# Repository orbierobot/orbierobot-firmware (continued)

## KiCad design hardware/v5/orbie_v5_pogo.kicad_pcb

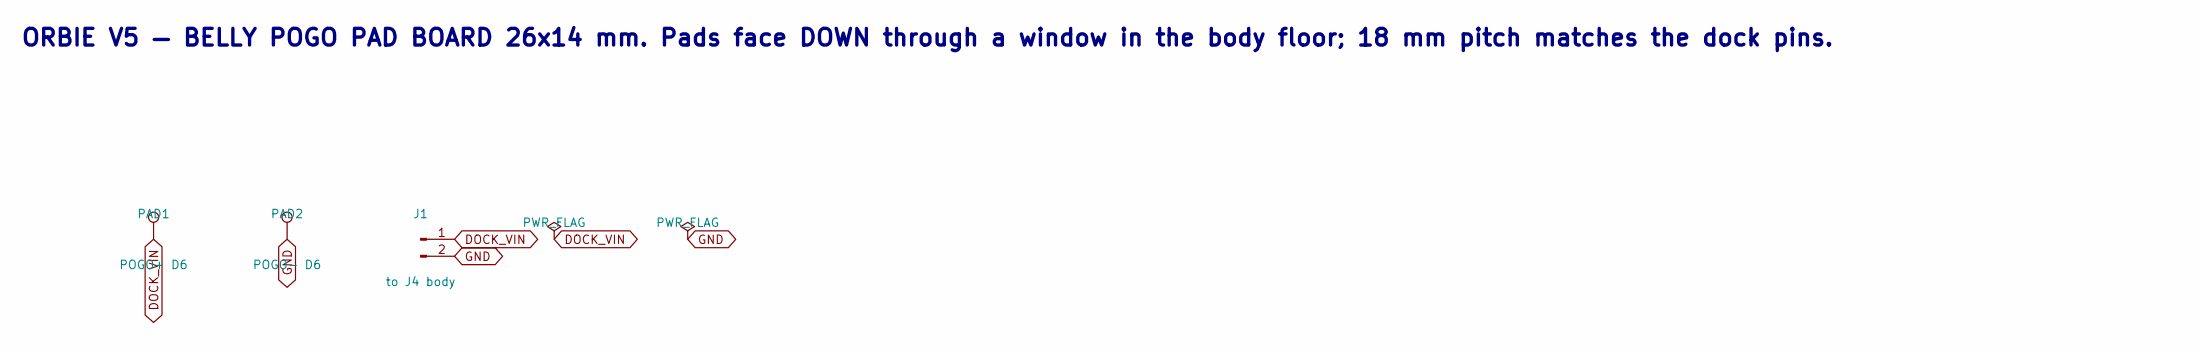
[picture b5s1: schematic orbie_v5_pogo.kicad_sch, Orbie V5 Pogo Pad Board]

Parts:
J1: to J4 body; JST_PH_B2B-PH-K_1x02_P2.00mm_Vertical
PAD1: POGO+ D6; PogoPad_D6mm
PAD2: POGO- D6; PogoPad_D6mm

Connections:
DOCK_VIN: J1.1, PAD1.1
GND: J1.2, PAD2.1

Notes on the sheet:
ORBIE V5 — BELLY POGO PAD BOARD 26x14 mm. Pads face DOWN through a window in the body floor; 18 mm pitch matches the dock pins.

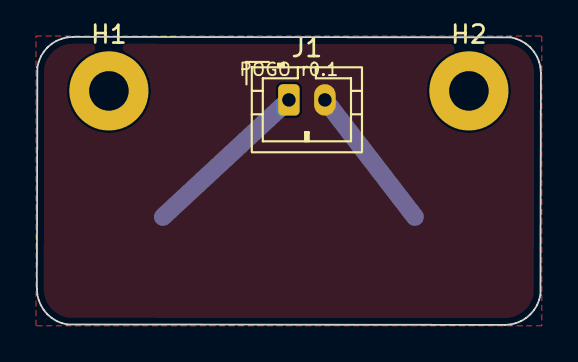
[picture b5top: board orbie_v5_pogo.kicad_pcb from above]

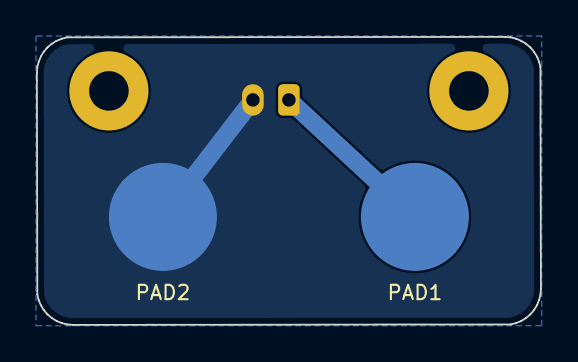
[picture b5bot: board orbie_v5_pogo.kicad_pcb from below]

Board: 2 copper layers, 28.0 x 16.0 mm, 5 parts (2 on the bottom side), 2 nets.

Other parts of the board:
H1, H2: MountingHole_2.2mm_M2_Pad

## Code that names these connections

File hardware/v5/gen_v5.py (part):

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                (40, 40), (0, 4, 0), "XIAO RP2040 left row D0..D6", "XIAO RP2040 right row (pins 8-14)")
    P += [a, b]
    P.append(C("C1", "10u", "+5V", "GND", (100, 34), (12, 10, 0), fp=HS_C8))
    P.append(Part("J13", "Connector", "Conn_01x02_Pin", "BUMPER switches (N.O., parallel)", ph(2), {"1": "BUMPER", "2": "GND"}, (120, 40), 0, (-30, 34, 0), desc="REQ-S5 contact detect"))
    # ---------------- IMU + ADC on the RP2040 bus
    T.append((160, 18, "U2 LSM6DS3 IMU on the axle line (REQ-S1/N2)   U16 ADS1015: AIN0/1 cliff IR (REQ-S4), AIN2/3 motor current via 0.1R on AISEN/BISEN (REQ-S5)", 2.0))
    imu = {"SDO/SA0": "GND", "SDX": None, "SCX": None, "INT1": "IMU_INT1", "VDDIO": "+3V3_RP", "GND": "GND", "VDD": "+3V3_RP",
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    P.append(R("R4", "5k1", "USB_CC1", "GND", (80, 215), (8, -38, 0), fp=HS_R))
    P.append(R("R5", "5k1", "USB_CC2", "GND", (80, 225), (24, -38, 0), fp=HS_R))
    P.append(two_pin("D6", "Diode", "SMAJ5.0A", "SMAJ5.0A TVS", "Diode_SMD:D_SMA", "GND", "VBUS", (80, 240), 0, (4, -42, 0), desc="USB surge"))
    P.append(Part("J4", "Connector", "Conn_01x02_Pin", "POGO pad board", ph(2), {"1": "DOCK_VIN", "2": "GND"}, (110, 220), 0, (-20, -43, 0), desc="to belly pads"))
    P.append(two_pin("D1", "Diode", "PMEG2005EJ", "PMEG2005EJ", "Diode_SMD:D_SOD-323F", "CHG_IN", "VBUS", (140, 210), 0, (6, -36, 0), desc="OR-ing"))
    P.append(two_pin("D2", "Diode", "PMEG2005EJ", "PMEG2005EJ", "Diode_SMD:D_SOD-323F", "CHG_IN", "DOCK_VIN_F", (140, 225), 0, (0, -36, 0), desc="OR-ing"))
    P.append(two_pin("F1", "Device", "Polyfuse_Small", "2A", "Fuse:Fuse_1206_3216Metric", "DOCK_VIN", "DOCK_VIN_F", (170, 225), 0, (-20, -36, 0)))
    chg = {"IN": "CHG_IN", "OUT": "VSYS", "BAT": "VBAT", "VSS": "GND", "~{CE}": "GND", "EN1": "GND", "EN2": "+3V3_E",
           "ILIM": "CHG_ILIM", "ISET": "CHG_ISET", "ITERM": "CHG_ITERM", "TMR": "CHG_TMR", "TS": "CHG_TS", "~{PGOOD}": "EXP_P1_PGOOD", "~{CHG}": "EXP_P0_CHG"}
    P.append(Part("U6", "Battery_Management", "BQ24074RGT", "BQ24074RGT", "Package_DFN_QFN:VQFN-16-1EP_3x3mm_P0.5mm_EP1.68x1.68mm", {}, (215, 225), 0, (-22, 8, 0), desc="1S charger + power path"))
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    P.append(R("R8", "1k5 (ITERM)", "CHG_ITERM", "GND", (285, 205), (-22, 16, 0), fp=HS_R))
    P.append(R("R9", "10k DNP (TS bypass)", "CHG_TS", "GND", (285, 215), (-22, 26, 0), fp=HS_R))
    P.append(R("R10", "10k (TMR)", "CHG_TMR", "GND", (285, 225), (-22, 29, 0), fp=HS_R))
    P.append(Part("J14", "Connector", "Conn_01x02_Pin", "NTC 10k on cells", ph(2), {"1": "CHG_TS", "2": "GND"}, (285, 245), 0, (-20, 34, 0), desc="REQ-P2 charge temperature interlock"))
    P.append(Part("J5", "Connector", "Conn_01x02_Pin", "BATT 1S2P 18650", "Connector_JST:JST_XH_B2B-XH-A_1x02_P2.50mm_Vertical",
                  {"1": "VBAT_CELLS", "2": "BAT_N"}, (320, 225), 0, (-31, -40, 90), desc="V3 pack (2 cells parallel)"))
    P.append(Part("SW1", "Switch", "SW_SPDT", "POWER", "Button_Switch_SMD:SW_SPDT_PCM12", {"1": None, "2": "VBAT_CELLS", "3": "VBAT"}, (350, 225), 0, (34, -38, 90), desc="main power"))
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    P.append(C("C10", "1u", "VBAT", "GND", (95, 300), (-16, 22, 0), fp=HS_C))
    boost = {"SW": "BOOST_SW", "GND": "GND", "FB": "BOOST_FB", "EN": "VSYS", "IN": "VSYS", "NC": None}
    P.append(Part("U8", "Regulator_Switching", "MT3608", "MT3608", "Package_TO_SOT_SMD:SOT-23-6", {}, (140, 310), 0, (20, 6, 0), desc="boost"))
    P.append(two_pin("L1", "Device", "L", "4u7 3A", "Inductor_SMD:L_Taiyo-Yuden_NR-40xx", "VSYS", "BOOST_SW", (180, 300), 0, (20, 14, 0)))
    P.append(two_pin("D3", "Diode", "SS14", "SS14", "Diode_SMD:D_SMA", "+5V", "BOOST_SW", (180, 310), 0, (26, 8, 90)))
    P.append(R("R11", "75k", "+5V", "BOOST_FB", (210, 300), (14, 2, 0), fp=HS_R))
    P.append(R("R12", "22k", "BOOST_FB", "GND", (210, 310), (18, 2, 0), fp=HS_R))
    P.append(C("C11", "22u", "+5V", "GND", (240, 300), (22, 27, 0), fp="Capacitor_SMD:C_1210_3225Metric_Pad1.33x2.70mm_HandSolder"))
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    P.append(R("R16", "10k", "+3V3_E", "FG_ALARM", (205, 395), (-25, -30, 0), fp=HS_R))
    T.append((230, 345, "J15/J16/J17  3x VL53L5CX 8x8 multizone ToF (front, left, right) on the body bus (REQ-N3 option A). Front LPn tied high; L/R LPn from the expander to assign addresses at boot", 2.0))
    for ref, side, pcbpos, lpn in (("J15", "FRONT", (-2, 42, 0), "+3V3_E"), ("J16", "LEFT", (-29, 14, 90), "TOF_LPN_L"), ("J17", "RIGHT", (29, 14, 90), "TOF_LPN_R")):
        P.append(Part(ref, "Connector", "Conn_01x06_Pin", f"VL53L5CX {side}", ph(6), {"1": "+3V3_E", "2": "GND", "3": "SDA_E", "4": "SCL_E", "5": lpn, "6": None},
                      (250 + {"FRONT": 0, "LEFT": 40, "RIGHT": 80}[side], 380), 0, pcbpos, desc="8x8 ToF module"))
    T.append((230, 400, "AUDIO  MAX98357A on +5V. JP2 GAIN strap: GND=12 dB | open=9 dB | VDD=6 dB, R20 100k->VDD = 3 dB (REQ-A2). Speaker: sealed-back 4R 3W (REQ-A1)", 2.0))
    amp = {"~{SD_MODE}": "+3V3_E", "NC": None, "GAIN_SLOT": "AMP_GAIN", "DIN": "I2S_DIN", "BCLK": "I2S_BCLK", "LRCLK": "I2S_LRC",
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    P.append(C("C17", "100n", "+5V", "GND", (285, 430), (4, 36, 0), fp=HS_C))
    P.append(Part("JP2", "Jumper", "SolderJumper_3_Open", "GAIN: GND | open | VDD", "Jumper:SolderJumper-3_P1.3mm_Open_RoundedPad1.0x1.5mm", {"1": "GND", "2": "AMP_GAIN", "3": "+5V"}, (320, 425), 0, (10, 32, 0), desc="amp gain strap"))
    P.append(R("R20", "100k DNP (3 dB)", "AMP_GAIN", "+5V", (320, 440), (16, 32, 0), fp=HS_R))
    P.append(Part("J6", "Connector", "Conn_01x02_Pin", "SPEAKER sealed 4R", ph(2), {"1": "SPK_P", "2": "SPK_N"}, (350, 430), 0, (36, 40, 90), desc="speaker"))
    # ---------------- harness, lidar, servo, dock sensing, reset/boot
    T.append((20, 470, "J7 NECK HARNESS 16p: GND +5V_HEAD 3V3 SDA_H SCL_H UART I2S SERVO IR_RX LIDAR_RX XIAO_RST XIAO_BOOT.  J12 LD19 lidar in the base (REQ-N4): 5V, TX->GPIO4 of the head XIAO.  SW2/SW3 recessed RESET/BOOT (REQ-X1..X4)", 2.0))
    neck = {"1": "GND", "2": "+5V_HEAD", "3": "+3V3_E", "4": "SDA_H", "5": "SCL_H", "6": "UART_RP_RX", "7": "UART_RP_TX", "8": "I2S_BCLK", "9": "I2S_LRC",
            "10": "I2S_DIN", "11": "SERVO_PWM", "12": "IR_RX", "13": "LIDAR_RX", "14": "XIAO_RST", "15": "XIAO_BOOT", "16": "GND"}
    P.append(Part("J7", "Connector", "Conn_01x16_Pin", "NECK HARNESS 16p", ph(16), neck, (45, 505), 0, (-37, 40, 0), desc="to head board"))
    T.append((60, 530, "head side: 6=GPIO1(TX) 7=GPIO2(RX) 12=GPIO3 13=GPIO4 14/15=XIAO RST/BOOT pads", 1.5))
    P.append(Part("J12", "Connector", "Conn_01x04_Pin", "LIDAR LD19 (5V GND TX PWM)", "Connector_JST:JST_ZH_B4B-ZR_1x04_P1.50mm_Vertical", {"1": "+5V", "2": "GND", "3": "LIDAR_RX", "4": None}, (110, 505), 0, (16, -12, 0), desc="360° lidar, base mounted"))
    P.append(Part("J9", "Connector", "Conn_01x03_Pin", "SERVO head tilt", ph(3), {"1": "SERVO_PWM", "2": "+5V_SERVO", "3": "GND"}, (150, 505), 0, (22, 34, 0), desc="SG90"))
    pfet = {"G": "SERVO_GATE", "S": "+5V", "D": "+5V_SERVO"}; nfet = {"G": "EXP_P3_SERVO_PWR_EN", "S": "GND", "D": "SERVO_GATE"}
    P.append(Part("Q1", "Transistor_FET", "AO3401A", "AO3401A", "Package_TO_SOT_SMD:SOT-23_Handsoldering", {}, (190, 495), 0, (14, -2, 0), desc="servo P-FET"))
    P.append(Part("Q2", "Transistor_FET", "AO3400A", "AO3400A", "Package_TO_SOT_SMD:SOT-23_Handsoldering", {}, (190, 520), 0, (28, -18, 0), desc="level shift"))
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    P.append(C("C18", "100n", "+3V3_E", "GND", (330, 495), (-20, -30, 0), fp=HS_C))
    P.append(Part("D4", "Device", "LED", "STATUS (ember)", "LED_SMD:LED_0603_1608Metric", {"1": "GND", "2": "LED_K"}, (360, 495), 0, (37, -44, 0)))
    P.append(R("R19", "1k", "+3V3_E", "LED_K", (360, 510), (33, -45, 0), fp=HS_R))
    P.append(Part("SW2", "Switch", "SW_Push", "RESET (pinhole)", "Button_Switch_SMD:SW_Push_SPST_NO_Alps_SKRK", {"1": "XIAO_RST", "2": "GND"}, (400, 495), 0, (-10, -44, 0), desc="side-actuated, through rear shell pinhole"))
    P.append(Part("SW3", "Switch", "SW_Push", "BOOT / hold 10 s = factory reset", "Button_Switch_SMD:SW_Push_SPST_NO_Alps_SKRK", {"1": "XIAO_BOOT", "2": "GND"}, (400, 520), 0, (-4, -44, 0), desc="side-actuated, through rear shell pinhole"))
    resolve_by_name(P, {"U2": imu, "U16": adc, "U3": drv, "U6": chg, "U7": fg, "U8": boost, "U9": ldo, "U14": prot, "Q3": q3, "Q4": q4,
                        "U15": buf, "U10": tca, "U11": amp, "Q1": pfet, "Q2": nfet, "U12": hall, "U13": ir})
    texts = [(20, 10, "ORBIE V5 — BODY CONTROLLER r0.2 (applies HW requirements 26 Sep 2026). Retrofit outline of the V3 Main PCB drawing — CONFIRM mounting pattern against the body before fab.", 3.0)] + T
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    name = "orbie_v5_pogo"
    P = [Part("PAD1", "Connector", "TestPoint", "POGO+ D6", "orbie_v5:PogoPad_D6mm", {"1": "DOCK_VIN"}, (40, 40), 0, (-7, -2, 0), side="B", desc="belly pad +"),
         Part("PAD2", "Connector", "TestPoint", "POGO- D6", "orbie_v5:PogoPad_D6mm", {"1": "GND"}, (60, 40), 0, (7, -2, 0), side="B", desc="belly pad -"),
         Part("J1", "Connector", "Conn_01x02_Pin", "to J4 body", ph(2), {"1": "DOCK_VIN", "2": "GND"}, (80, 40), 0, (0, 4.5, 0), desc="to body J4")]
    texts = [(20, 10, "ORBIE V5 — BELLY POGO PAD BOARD 28x16 mm. Pads face DOWN through a window in the body floor; 14 mm pitch matches the dock pins.", 2.5)]
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
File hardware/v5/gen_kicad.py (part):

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    P.append(C("C1", "100n", "+3V3", "GND", (185, 34), (-22, 3, 0)))
    # ---- Motor driver
    T.append((20, 90, "U2  DRV8833 dual H-bridge — N20 gearmotors L/R, VM from VSYS (option: +5V boost for more torque)", 2.0))
    drv = {"VM": "VSYS", "GND": "GND", "VCP": "DRV_VCP", "VINT": "DRV_VINT", "AIN1": "GPIO1_MOTA_FWD", "AIN2": "GPIO2_MOTA_REV",
           "BIN1": "GPIO4_MOTB_FWD", "BIN2": "GPIO3_MOTB_REV", "AOUT1": "MOTA_1", "AOUT2": "MOTA_2", "BOUT1": "MOTB_1", "BOUT2": "MOTB_2",
           "AISEN": "GND", "BISEN": "GND", "~{SLEEP}": "EXP_P6_DRV_nSLEEP", "~{FAULT}": "EXP_P7_DRV_nFAULT"}
    P.append(Part("U2", "Driver_Motor", "DRV8833PWP", "DRV8833PWP", "Package_SO:HTSSOP-16-1EP_4.4x5mm_P0.65mm_EP3.4x5mm",
                  drv, (60, 120), 0, (-24, -8, 0), desc="dual H-bridge 1.5A"))
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    T.append((60, 232, "USB D+/D- go to the head FPC only if the XIAO USB is exposed there; default: NC (XIAO has its own USB-C for flashing)", 1.5))
    P.append(Part("TP1", "Connector", "TestPoint", "DOCK+ pogo pad Ø3", "TestPoint:TestPoint_Pad_3.0x3.0mm", {"1": "DOCK_VIN"}, (110, 195), 0, (-18, -20, 0), side="B", desc="dock pogo +"))
    P.append(Part("TP2", "Connector", "TestPoint", "DOCK- pogo pad Ø3", "TestPoint:TestPoint_Pad_3.0x3.0mm", {"1": "GND"}, (110, 210), 0, (18, -20, 0), side="B", desc="dock pogo -"))
    P.append(two_pin("D1", "Diode", "PMEG2005EJ", "PMEG2005EJ", "Diode_SMD:D_SOD-323F", "CHG_IN", "VBUS", (140, 195), 0, (-8, -30, 0), desc="OR-ing"))
    P.append(two_pin("D2", "Diode", "PMEG2005EJ", "PMEG2005EJ", "Diode_SMD:D_SOD-323F", "CHG_IN", "DOCK_VIN", (140, 210), 0, (8, -30, 0), desc="OR-ing"))
    P.append(two_pin("F1", "Device", "Polyfuse_Small", "2A", "Fuse:Fuse_1206_3216Metric", "DOCK_VIN", "DOCK_VIN_F", (170, 210), 0, (0, -30, 0)))
    # charger BQ24074: pin names
    chg = {"IN": "CHG_IN", "OUT": "VSYS", "BAT": "VBAT", "VSS": "GND", "~{CE}": "GND", "EN1": "GND", "EN2": "+3V3",
           "ILIM": "CHG_ILIM", "ISET": "CHG_ISET", "ITERM": "CHG_ITERM", "TMR": "CHG_TMR", "TS": "CHG_TS", "~{PGOOD}": "EXP_P5_CHG_PGOOD",
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                  {}, (335, 210), 0, (20, -18, 0), desc="fuel gauge"))
    P.append(C("C12", "1u", "VBAT", "GND", (370, 200), (26, -24, 0)))
    # boost 5V
    T.append((20, 255, "U8  MT3608 boost VSYS->5V @2A (servo, XIAO 5V pin, audio, head LED drivers)    U9  AP2112K 3.3V LDO (IMU, expander, sensors)", 2.0))
    boost = {"SW": "BOOST_SW", "GND": "GND", "FB": "BOOST_FB", "EN": "VSYS", "IN": "VSYS", "NC": None}
    P.append(Part("U8", "Regulator_Switching", "MT3608", "MT3608", "Package_TO_SOT_SMD:SOT-23-6", {}, (60, 285), 0, (16, -8, 0), desc="boost"))
    P.append(two_pin("L1", "Device", "L", "4u7 3A", "Inductor_SMD:L_Taiyo-Yuden_NR-40xx", "VSYS", "BOOST_SW", (100, 275), 0, (24, -8, 0)))
    P.append(two_pin("D3", "Diode", "SS14", "SS14", "Diode_SMD:D_SMA", "+5V", "BOOST_SW", (100, 285), 0, (24, -14, 0)))
    P.append(R("R10", "75k", "+5V", "BOOST_FB", (130, 275), (16, -13, 0)))
    P.append(R("R11", "22k", "BOOST_FB", "GND", (130, 285), (16, -15, 0)))
    P.append(C("C14", "22u", "+5V", "GND", (160, 275), (30, -8, 0), fp="Capacitor_SMD:C_1210_3225Metric"))
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    P.append(Part("U11", "Interface_Optical", "TSOP38G36", "IRM-H638T (38kHz)", "OptoDevice:Everlight_IRM-H6xxT", {}, (380, 285), 0, (-14, -36, 90), side="B", desc="IR receiver"))
    P.append(C("C18", "100n", "+3V3", "GND", (410, 275), (-14, -30, 0), side="B"))
    # ---- Head FPC + servo + power switch
    T.append((20, 320, "J7  12-pin FPC to HEAD board: 3V3 5V GND SDA SCL SDB LASER_EN SERVO_PWM IMU/EXP INT  |  J5 head tilt servo (power gated by U12)  |  SW1 main power", 2.0))
    fpc = {"1": "GND", "2": "+5V_SERVO", "3": "+5V", "4": "+3V3", "5": "SDA", "6": "SCL", "7": "EXP_P0_LASER_EN", "8": "LED_SDB",
           "9": "GPIO43_SERVO_PWM", "10": "EXP_INT", "11": "GND", "12": "GND", "MP": "GND"}
    P.append(Part("J7", "Connector", "Conn_01x12_Pin", "HEAD FPC 12p", "Connector_FFC-FPC:Hirose_FH12-12S-0.5SH_1x12-1MP_P0.50mm_Horizontal",
                  fpc, (45, 355), 0, (0, 42, 180), desc="head harness"))
    P.append(Part("J5", "Connector", "Conn_01x03_Pin", "SERVO SG90", "Connector_JST:JST_PH_B3B-PH-K_1x03_P2.00mm_Vertical",
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
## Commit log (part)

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2026-06-16 added sound, motors, laser.
